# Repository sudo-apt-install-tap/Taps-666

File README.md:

# TAPS-666

## Introduction
Taps-666 is a simple LED blinker PCB designed in KiCAD.  
It uses only discrete components and does not rely on any firmware or microcontroller.  
The project is intended as a minimal hardware reference and learning build.

## Images

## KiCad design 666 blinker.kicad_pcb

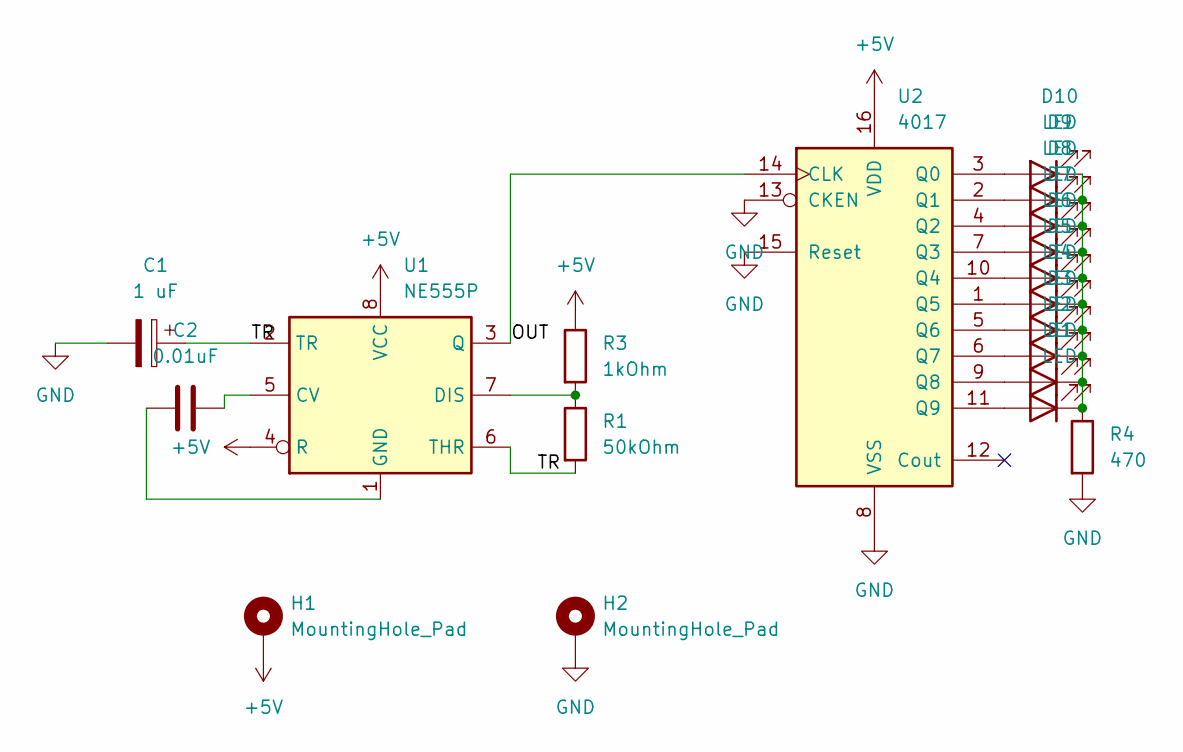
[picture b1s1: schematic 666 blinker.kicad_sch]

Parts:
C1: 1 uF; CP_Radial_D5.0mm_P2.00mm
C2: 0.01uF; CP_Radial_D5.0mm_P2.00mm
D1, D2, D3, D4, D5, D6, D7, D8, D9, D10: LED; LED_D3.0mm
H1, H2: MountingHole_Pad; PinHeader_1x01_P2.54mm_Horizontal
R1: 50kOhm; R_Axial_DIN0207_L6.3mm_D2.5mm_P7.62mm_Horizontal
R3: 1kOhm; R_Axial_DIN0207_L6.3mm_D2.5mm_P7.62mm_Horizontal
R4: 470; R_Axial_DIN0207_L6.3mm_D2.5mm_P7.62mm_Horizontal
U1: NE555P; DIP-8_W7.62mm
U2: 4017; Texas_RGY_R-PVQFN-N16_EP2.05x2.55mm

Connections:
+5V: H1.1, R3.1, U1.4 (R), U1.8 (VCC), U2.16 (VDD)
/OUT: U1.3 (Q), U2.14 (CLK)
/TR: C1.1, R1.2, U1.2 (TR), U1.6 (THR)
GND: C1.2, H2.1, R4.2, U2.8 (VSS), U2.13 (CKEN), U2.15 (Reset)
unnamed: D1.2 (A), U2.11 (Q9)
unnamed: D1.1 (K), D2.1 (K), D3.1 (K), D4.1 (K), D5.1 (K), D6.1 (K), D7.1 (K), D8.1 (K), D9.1 (K), D10.1 (K), R4.1
unnamed: D2.2 (A), U2.9 (Q8)
unnamed: D3.2 (A), U2.6 (Q7)
unnamed: D4.2 (A), U2.5 (Q6)
unnamed: D5.2 (A), U2.1 (Q5)
unnamed: D6.2 (A), U2.10 (Q4)
unnamed: D7.2 (A), U2.7 (Q3)
unnamed: D8.2 (A), U2.4 (Q2)
unnamed: D9.2 (A), U2.2 (Q1)
unnamed: D10.2 (A), U2.3 (Q0)
unnamed: C2.2, U1.5 (CV)
unnamed: R1.1, R3.2, U1.7 (DIS)
unnamed: C2.1, U1.1 (GND)

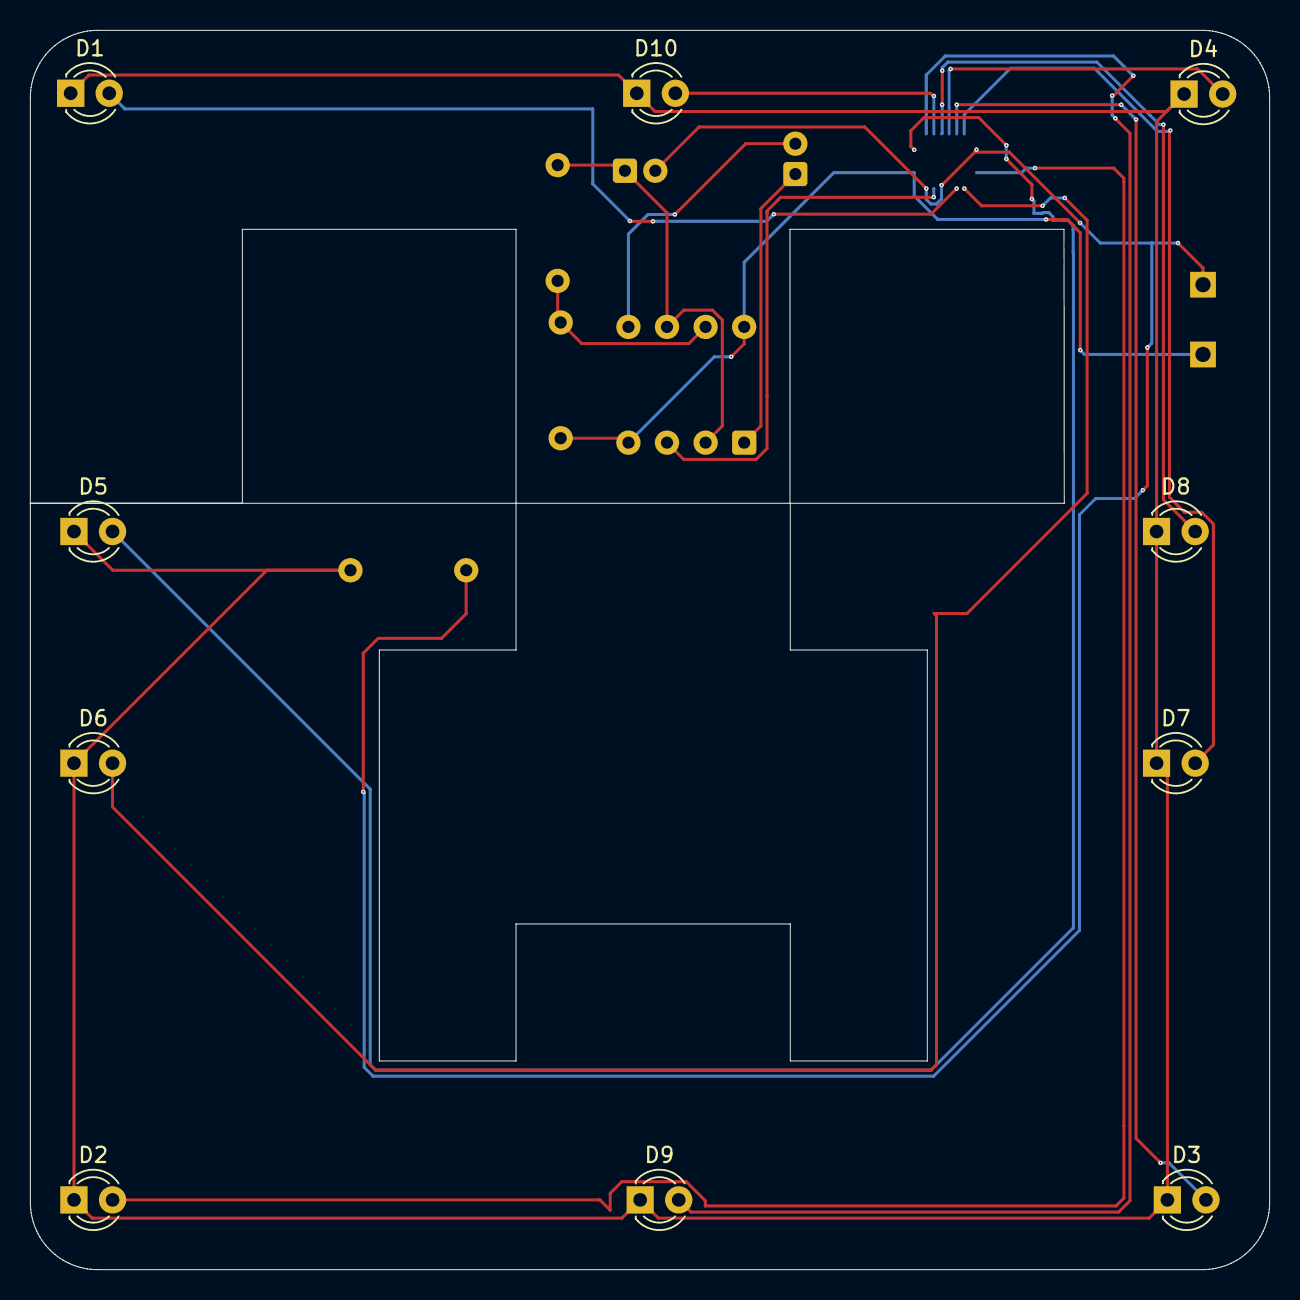
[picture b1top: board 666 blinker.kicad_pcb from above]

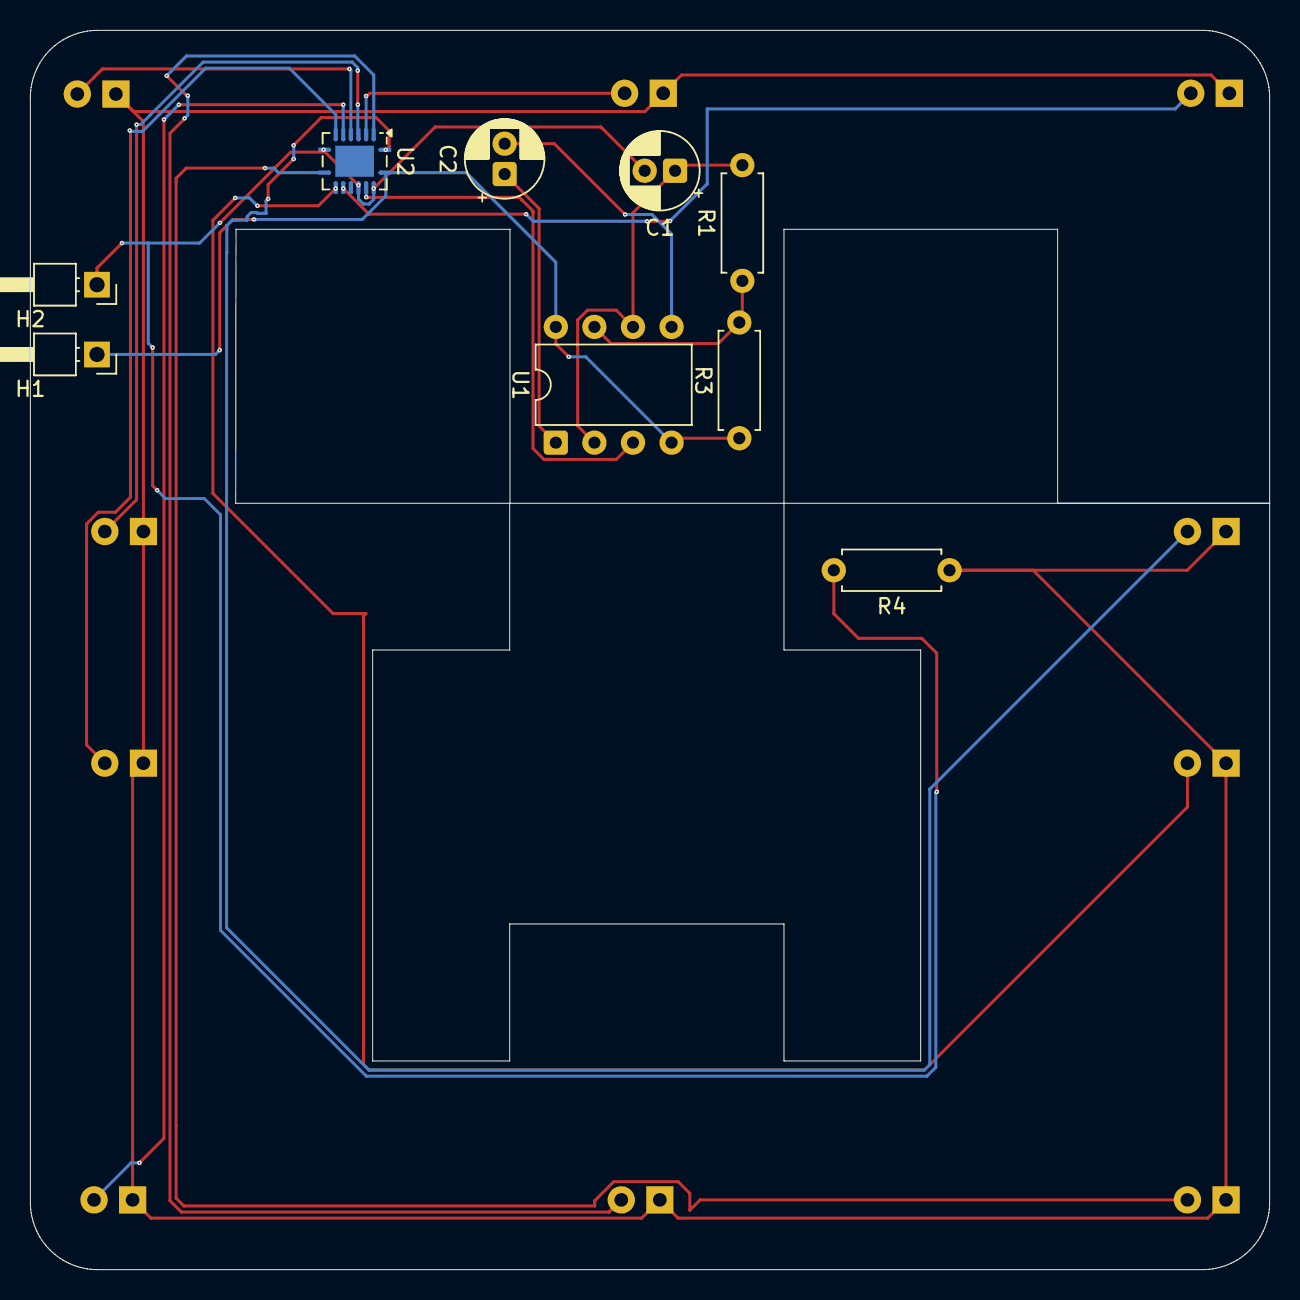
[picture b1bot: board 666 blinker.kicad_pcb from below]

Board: 2 copper layers, 81.6 x 81.6 mm, 19 parts (9 on the bottom side), 18 nets.

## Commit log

2026-01-20 added README.MD
2026-01-20 Enhance README with introduction and images
    Added introduction section and images for TAPS-666 project.
